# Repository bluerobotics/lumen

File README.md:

# *Lumen* Subsea Lights

The *Lumen* Subsea Light is an underwater, pressure-rated LED light capable of outputting over 1500 lumens. 

The schematic and board layout are designed in EagleCAD.

# *Lumen* Subsea Light Hardware

## Features 

* 1500+ lm output
* Onboard microcontroller (ATTiny45) for programmable behavior
* Multiple signal input types:
	* Standard servo PWM input signal (1100-1900 microseconds)
	* Direct duty cycle control (with solder jumper)
	* On/off control with no signal needed by connecting signal wire to power
* Daisy-chainable to allow multiple lights from a single cable
* Thermistor temperature feedback and overheating protection
* 6-48V input range
* 0-2.5A LED output

## Software

The software running on the onboard microcontroller is available in the *Lumen-Arduino* directory and can be installed with the Arduino IDE and an AVR-ISP programmer.

## License

The Lumen Subsea Light Hardware Design is released under the MIT License.

## Revision History

0.0 - Under development

0.1 - First production version

0.11 - First production version w/ software

0.20 - Lumen R2 launch firmware

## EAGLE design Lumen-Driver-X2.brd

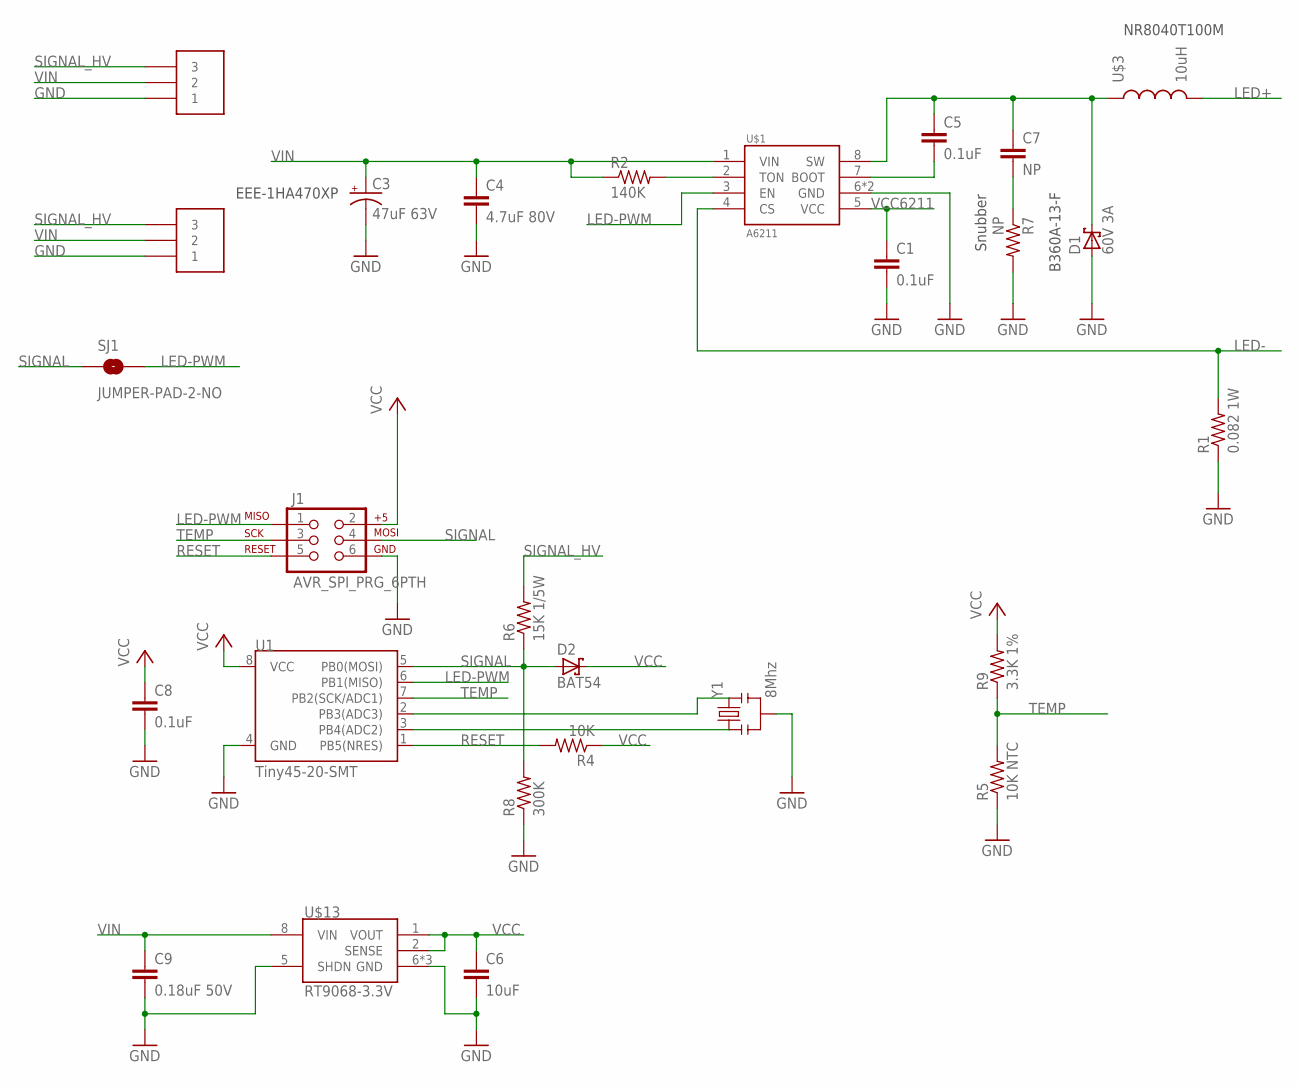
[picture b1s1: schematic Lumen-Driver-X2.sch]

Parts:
C1, C5, C8: 0.1uF; C0402
C3: 47uF 63V; PANASONIC_D
C4: 4.7uF 80V; C1210
C6: 10uF; C0603
C7: NP; C0603
C9: 0.18uF 50V; C0805
D1: 60V 3A; SMA
D2: BAT54; SOD523
J1: AVR_SPI_PRG_6PTH; 2X3
R1: 0.082 1W; R2512
R2: 140K; R0402
R4: 10K; R0402
R5: 10K NTC; R0603
R6: 15K 1/5W; R0402
R7: NP; R1206
R8: 300K; R0402
R9: 3.3K 1%; R0402
SJ1: JUMPER-PAD-2-NO; PAD-JUMPER-2-NO_NO_SILK
U1: Tiny45-20-SMT; SO08-EIAJ
U$1: A6211; SOIC8N-LJ
U$3: 10uH; INDUCTOR-8040
U$11, U$12: 009176003032006; AVX-9176-3POS
U$13: RT9068-3.3V; SOIC8N-LJ
Y1: 8Mhz; RESONATOR-SMD

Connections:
GND: C1.2, C3.-, C4.2, C6.2, C8.2, C9.2, D1.A, J1.6, R1.1, R5.1, R7.2, R8.1, U1.4 (GND), U$1.6 (GND), U$1.PAD (GND), U$11.1, U$12.1, U$13.5 (SHDN), U$13.6 (GND), U$13.7 (GND), U$13.PAD (GND), Y1.2
LED+: U$3.P$2 (2)
LED-: R1.2, U$1.4 (CS)
LED-PWM: J1.1, SJ1.2, U1.6 (PB1(MISO)), U$1.3 (EN)
unnamed: R2.2, U$1.2 (TON)
unnamed: C7.2, R7.1
unnamed: C5.2, U$1.7 (BOOT)
unnamed: C5.1, C7.1, D1.C, U$1.8 (SW), U$3.P$1 (1)
unnamed: U1.3 (PB4(ADC2)), Y1.1
unnamed: U1.2 (PB3(ADC3)), Y1.3
RESET: J1.5, R4.2, U1.1 (PB5(NRES))
SIGNAL: D2.A, J1.4, R6.1, R8.2, SJ1.1, U1.5 (PB0(MOSI))
SIGNAL_HV: R6.2, U$11.3, U$12.3
TEMP: J1.3, R5.2, R9.1, U1.7 (PB2(SCK/ADC1))
VCC: C6.1, C8.1, D2.C, J1.2, R4.1, R9.2, U1.8 (VCC), U$13.1 (VOUT), U$13.2 (SENSE)
VCC6211: C1.1, U$1.5 (VCC)
VIN: C3.+, C4.1, C9.1, R2.1, U$1.1 (VIN), U$11.2, U$12.2, U$13.8 (VIN)

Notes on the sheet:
NR8040T100M
B360A-13-F
Snubber
EEE-1HA470XP

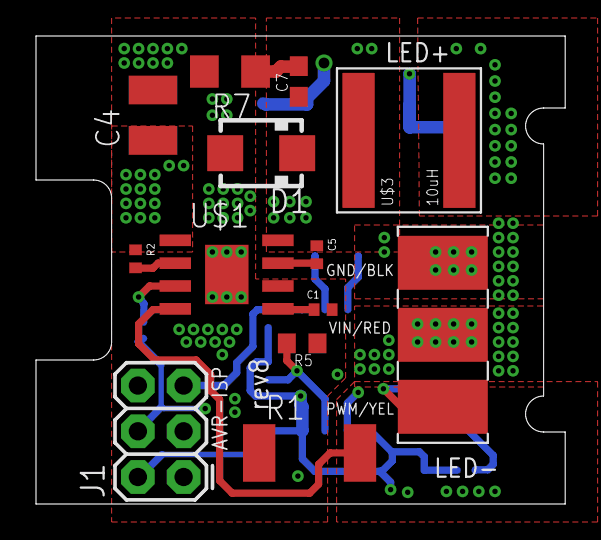
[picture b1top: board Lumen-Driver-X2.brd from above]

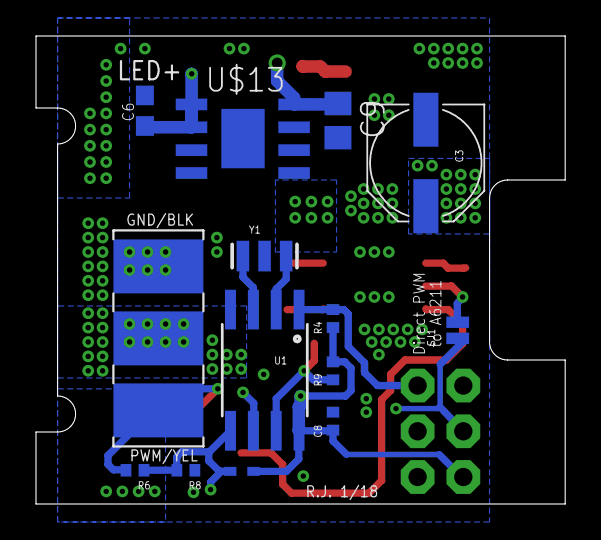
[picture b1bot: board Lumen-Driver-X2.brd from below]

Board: 4 copper layers, 29.4 x 26.0 mm, 27 parts (14 on the bottom side), 16 nets.

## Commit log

2015-11-24 Added more notes to README.
2015-11-24 Added starter file for schematic.
2015-12-06 Added main components to schematic and wired.
2015-12-06 Added thermistor.
2015-12-09 Added completed board layout and made some changes to the schematic. Nearly ready for prototype.
2015-12-12 Fixed a lot of little things. Added regulator back into the design. Upgrade capacitor voltage ratings.
2015-12-13 Add first revision of the software. Arduino compatible because it's so easy and took 10 minutes to write. This is totally untested because the hardware does not yet exist.
2015-12-14 Fixed some layout issues per John's suggestion. Added pads for a snubber that will probably not be populated.
2015-12-15 More updates based on J.N. comments. Ready to order I believe.
2015-12-15 Minor update to markings for clarity.
2015-12-15 Fixed two minor issues in the layout with ground per J.N. suggestion. Ordering a prototype tomorrow.
2016-01-25 Added thermistor curve calculation program for Matlab/Octave.
2016-01-25 Updates to Arduino program based on testing and further study.
2016-01-28 Software: Working! Dimming working well.
2016-01-28 Updated software for better overtemp limiting.
2016-02-01 Adjusted signal pull-down for 3.3V compatibility.
2016-02-04 Minor code updates.
2016-02-10 Readme updates to reflect most recent version.
2016-02-10 Added PDF schematic.
2016-02-11 Change LED PWM frequency to 3900 Hz to avoid conflict with low frame-rate cameras
2016-02-11 Added comment about higher frequency.
2016-02-19 Adjustments for 2 oz copper boards.
2016-02-19 Added shell script for programming.
2016-03-01 Update temperature values.
2016-03-02 Rearranged boards for manufacturability. Changed 0402 footprint.
2016-04-06 Small updates for schematic and board.
2016-04-13 Updates before launch.
2016-04-21 Rewrite pulse function to be smart and handle noisy low-voltage signals like Pixhawk.
2016-05-23 Minor update to rev4 with larger solder holes for capacitor and silkscreen changes.
2016-05-28 Minor layout updates for new production order.
2016-08-25 Make signal input more noise resistant.
2018-01-06 Rev6 as produced with IDC connector.
2018-02-28 Re-layout board for new size. In progress.
2018-04-25 Updated R2 design. Ordered and tested.
2018-06-08 Minor updates.
2018-06-29 updated driver.
2018-06-29 Reformat #defines
2018-06-29 Move #defines to header file
2018-06-29 Reorganize code
2018-06-29 Increase timer 0 speed for better resolution
2018-06-29 Use hardware timers, interrupts for PWM input/output
2018-06-29 Add hex file
2018-06-29 Increase number of brightness steps
2018-06-29 Use sliding hysteresis for temperature control
2018-06-29 Use sliding hysteresis window
2018-06-29 Use more generic pseudo-exponential mapping function
2018-06-29 Filter and discretize input
2018-06-29 Update Lumen programming script
2018-06-29 Replace temp PID with P controller
2018-06-29 Use exponential mapping
2018-06-29 Fix millis() overflow bug
2018-06-29 Prevent interrupts from interrupting volatile multi-byte values
2018-06-29 Update Revision History
2018-06-29 Add pulse check for compatibility w/ 5 V Lumens
2018-06-29 Update hex file
2020-04-01 Update PDF schematic.

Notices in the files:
parts and their libraries:
SparkFun-Capacitors: Licensing: Creative Commons ShareAlike 4.0 International - https://creativecommons.org/licenses/by-sa/4.0
